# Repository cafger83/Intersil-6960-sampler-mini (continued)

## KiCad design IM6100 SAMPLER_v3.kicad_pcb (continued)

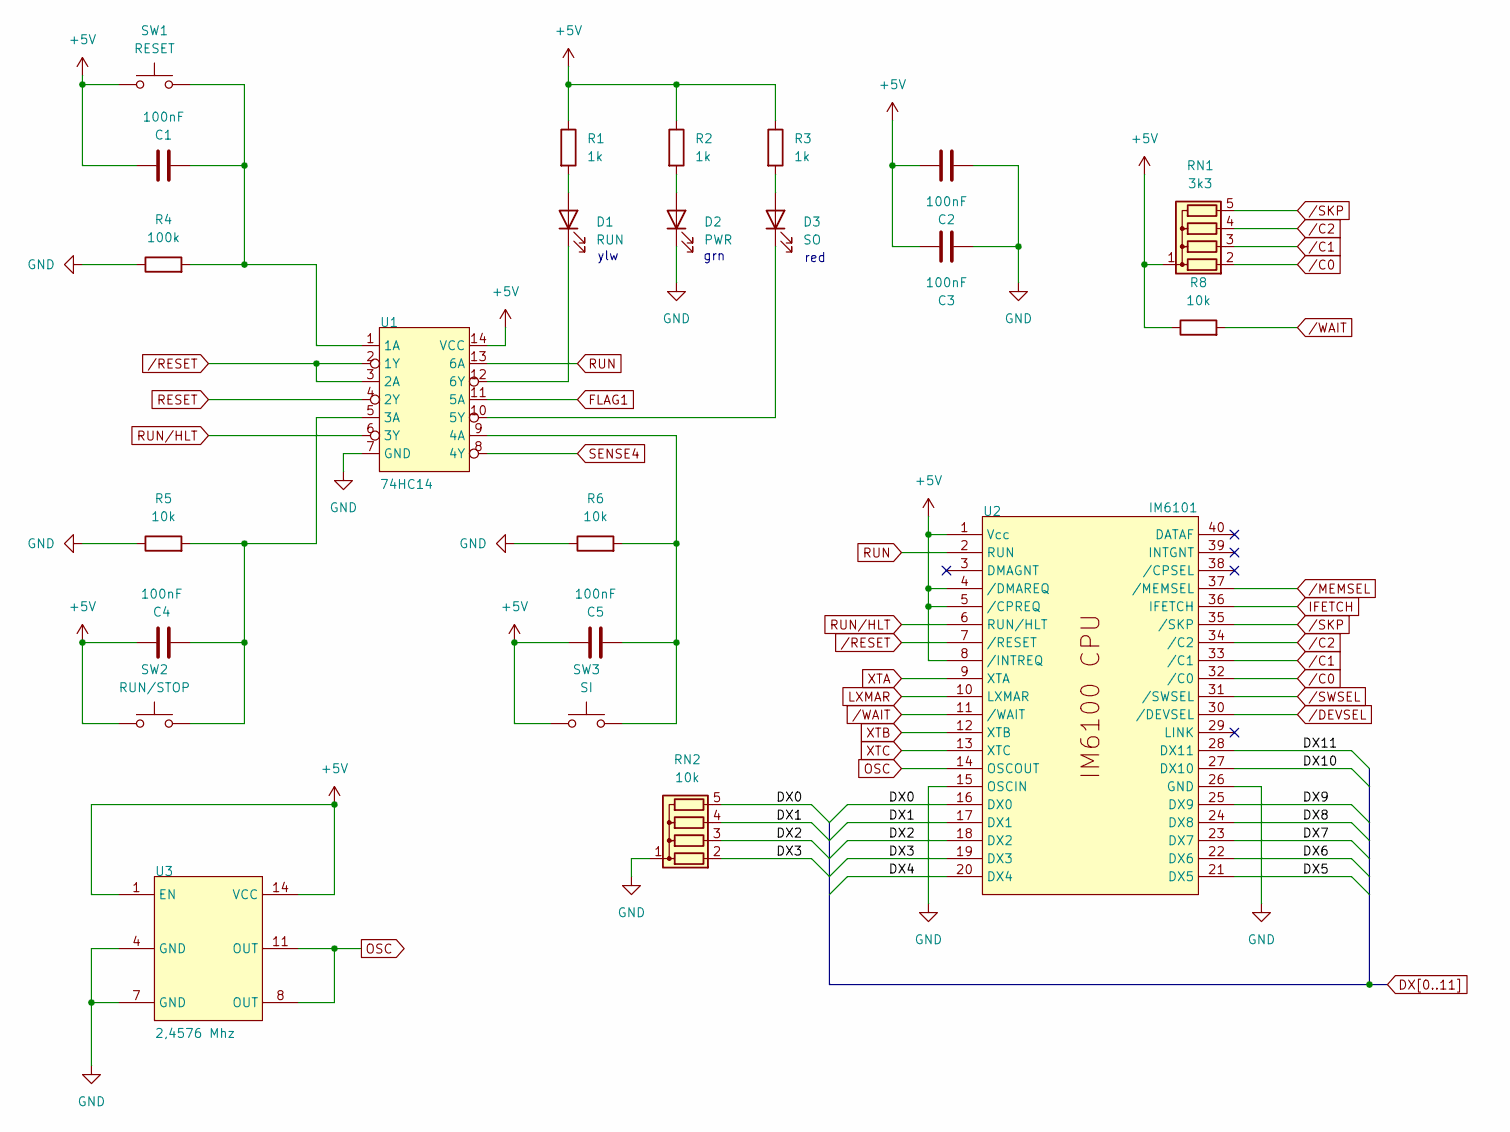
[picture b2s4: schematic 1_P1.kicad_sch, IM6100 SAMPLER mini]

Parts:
C1, C2, C3, C4, C5: 100nF; C_Disc_D5.0mm_W2.5mm_P2.50mm
D1: RUN; LED_D3.0mm
D2: PWR; LED_D3.0mm
D3: SO; LED_D3.0mm
R1, R2, R3: 1k; R_Axial_DIN0207_L6.3mm_D2.5mm_P7.62mm_Horizontal
R4: 100k; R_Axial_DIN0207_L6.3mm_D2.5mm_P7.62mm_Horizontal
R5, R6, R8: 10k; R_Axial_DIN0207_L6.3mm_D2.5mm_P7.62mm_Horizontal
RN1: 3k3; R_Array_SIP5
RN2: 10k; R_Array_SIP5
SW1: RESET; SW_PUSH_1P1T_6x3.5mm_H5.0_APEM_MJTP1250
SW2: RUN/STOP; SW_PUSH_1P1T_6x3.5mm_H5.0_APEM_MJTP1250
SW3: SI; SW_PUSH_1P1T_6x3.5mm_H5.0_APEM_MJTP1250
U1: 74HC14; DIP-14_W7.62mm_Socket
U2: IM6101; DIP-40_W15.24mm_Socket
U3: 2,4576 Mhz; DIP-14_W7.62mm_Socket

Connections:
+5V: C1.2, C2.2, C3.2, C4.2, C5.2, R1.1, R2.1, R3.1, R8.1, RN1.1 (common), SW1.1, SW2.1, SW3.1, U1.14 (VCC), U2.1 (Vcc), U2.4 (/DMAREQ), U2.5 (/CPREQ), U2.8 (/INTREQ), U3.1 (EN), U3.14 (VCC); also elsewhere on the board
DX0: RN2.5 (R4), U2.16 (DX0); also elsewhere on the board
DX1: RN2.4 (R3), U2.17 (DX1); also elsewhere on the board
DX2: RN2.3 (R2), U2.18 (DX2); also elsewhere on the board
DX3: RN2.2 (R1), U2.19 (DX3); also elsewhere on the board
DX4: U2.20 (DX4); also elsewhere on the board
DX5: U2.21 (DX5); also elsewhere on the board
DX6: U2.22 (DX6); also elsewhere on the board
DX7: U2.23 (DX7); also elsewhere on the board
DX8: U2.24 (DX8); also elsewhere on the board
DX9: U2.25 (DX9); also elsewhere on the board
DX10: U2.27 (DX10); also elsewhere on the board
DX11: U2.28 (DX11); also elsewhere on the board
FLAG1: U1.11 (5A); also elsewhere on the board
GND: C2.1, C3.1, D2.1 (K), R4.1, R5.1, R6.1, RN2.1 (common), U1.7 (GND), U2.15 (OSCIN), U2.26 (GND), U3.4 (GND), U3.7 (GND); also elsewhere on the board
IFETCH: U2.36 (IFETCH); also elsewhere on the board
LXMAR: U2.10 (LXMAR); also elsewhere on the board
unnamed: D1.2 (A), R1.2
unnamed: D1.1 (K), U1.12 (6Y)
unnamed: D2.2 (A), R2.2
unnamed: D3.2 (A), R3.2
unnamed: D3.1 (K), U1.10 (5Y)
unnamed: C1.1, R4.2, SW1.2, U1.1 (1A)
unnamed: C4.1, R5.2, SW2.2, U1.5 (3A)
unnamed: C5.1, R6.2, SW3.2, U1.9 (4A)
OSC: U2.14 (OSCOUT), U3.8 (OUT), U3.11 (OUT); also elsewhere on the board
RESET: U1.4 (2Y); also elsewhere on the board
RUN: U1.13 (6A), U2.2 (RUN)
RUN/HLT: U1.6 (3Y), U2.6 (RUN/HLT)
SENSE4: U1.8 (4Y); also elsewhere on the board
XTA: U2.9 (XTA); also elsewhere on the board
XTB: U2.12 (XTB); also elsewhere on the board
XTC: U2.13 (XTC); also elsewhere on the board
/C0: RN1.2 (R1), U2.32 (/C0); also elsewhere on the board
/C1: RN1.3 (R2), U2.33 (/C1); also elsewhere on the board
/C2: RN1.4 (R3), U2.34 (/C2); also elsewhere on the board
/DEVSEL: U2.30 (/DEVSEL); also elsewhere on the board
/MEMSEL: U2.37 (/MEMSEL); also elsewhere on the board
/SKP: RN1.5 (R4), U2.35 (/SKP); also elsewhere on the board
/SWSEL: U2.31 (/SWSEL); also elsewhere on the board
/WAIT: R8.2, U2.11 (/WAIT); also elsewhere on the board

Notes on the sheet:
grn
ylw
red

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
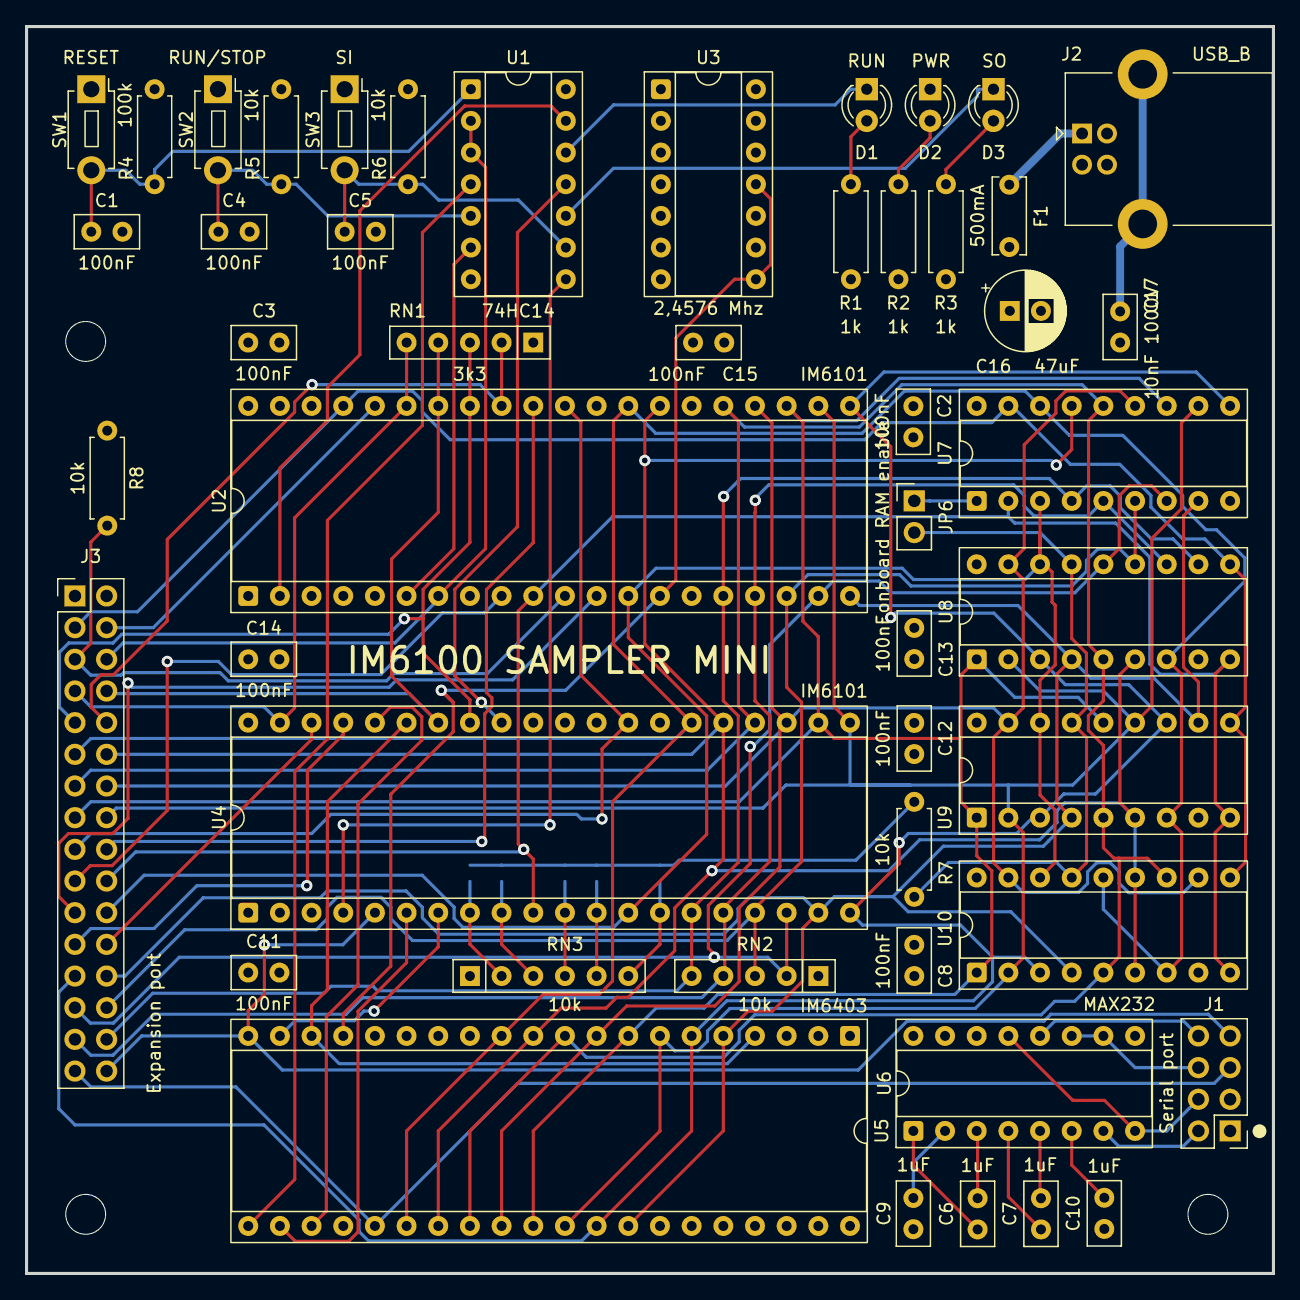
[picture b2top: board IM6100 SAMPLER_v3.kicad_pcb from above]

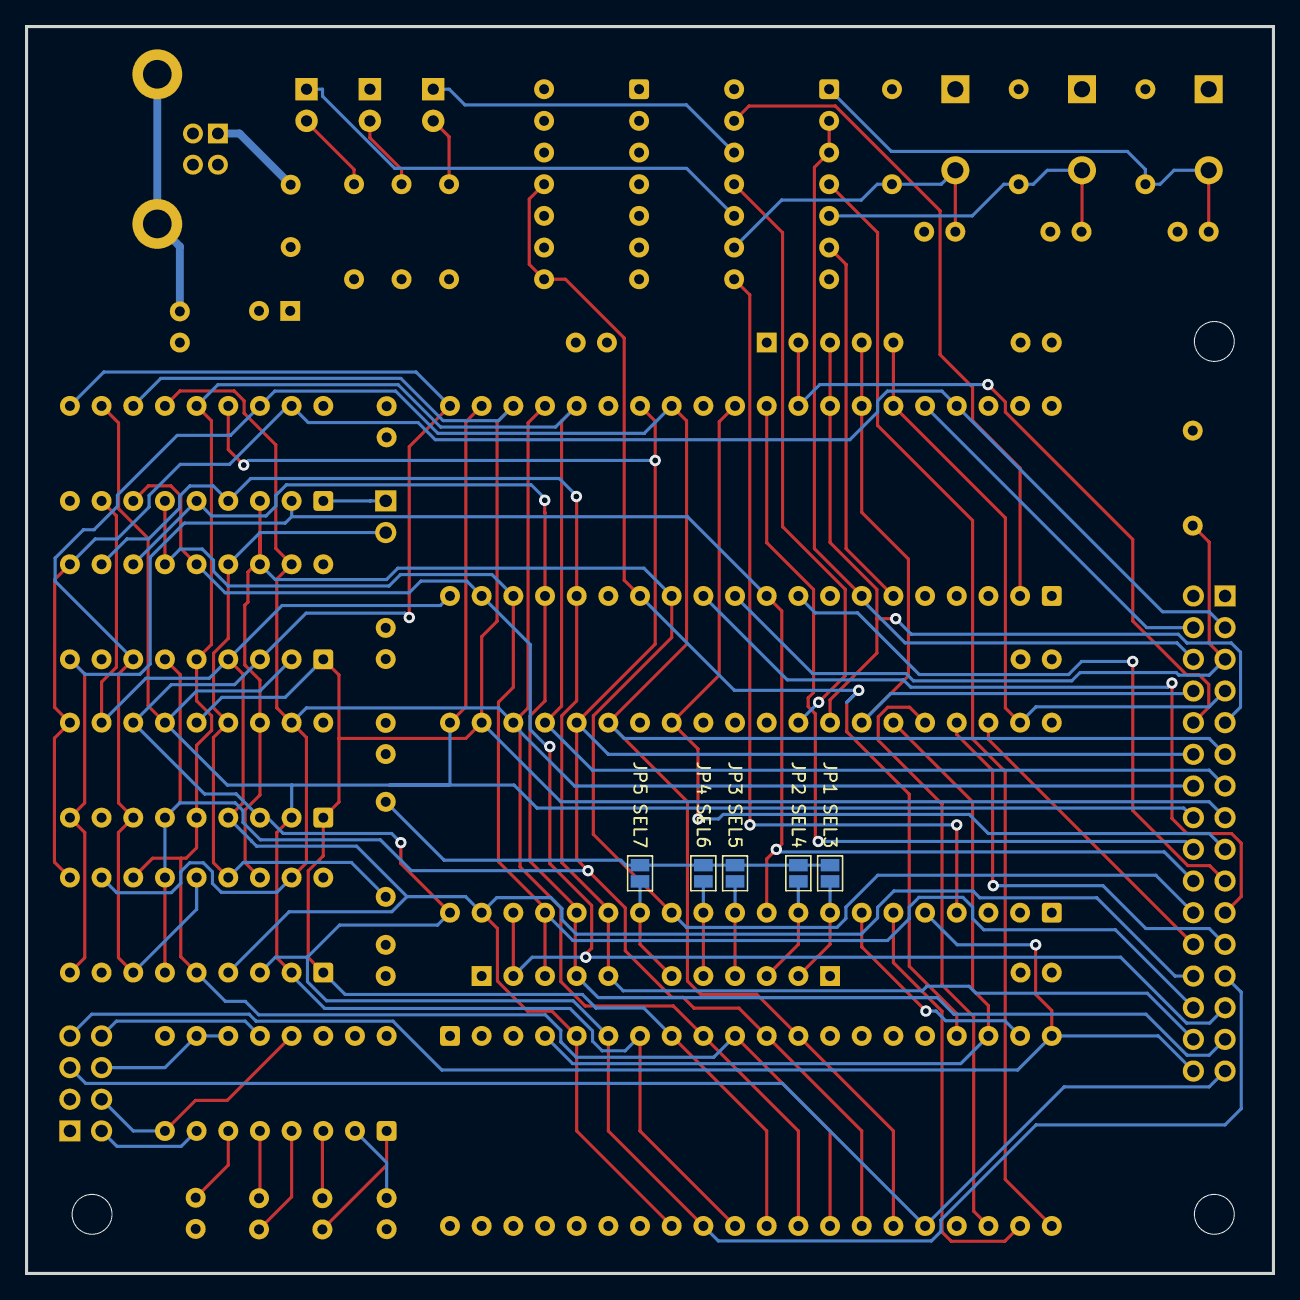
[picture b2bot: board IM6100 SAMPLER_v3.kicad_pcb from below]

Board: 4 copper layers, 100.0 x 100.0 mm, 57 parts (5 on the bottom side), 69 nets.

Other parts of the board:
HOLE2, HOLE3, HOLE4: MountingHole_3.2mm_M3

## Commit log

2025-04-20 New board version with mounting holes
2025-04-20 Refactoring the files
2025-04-24 creating HID board
2025-04-27 HID board finalizing
